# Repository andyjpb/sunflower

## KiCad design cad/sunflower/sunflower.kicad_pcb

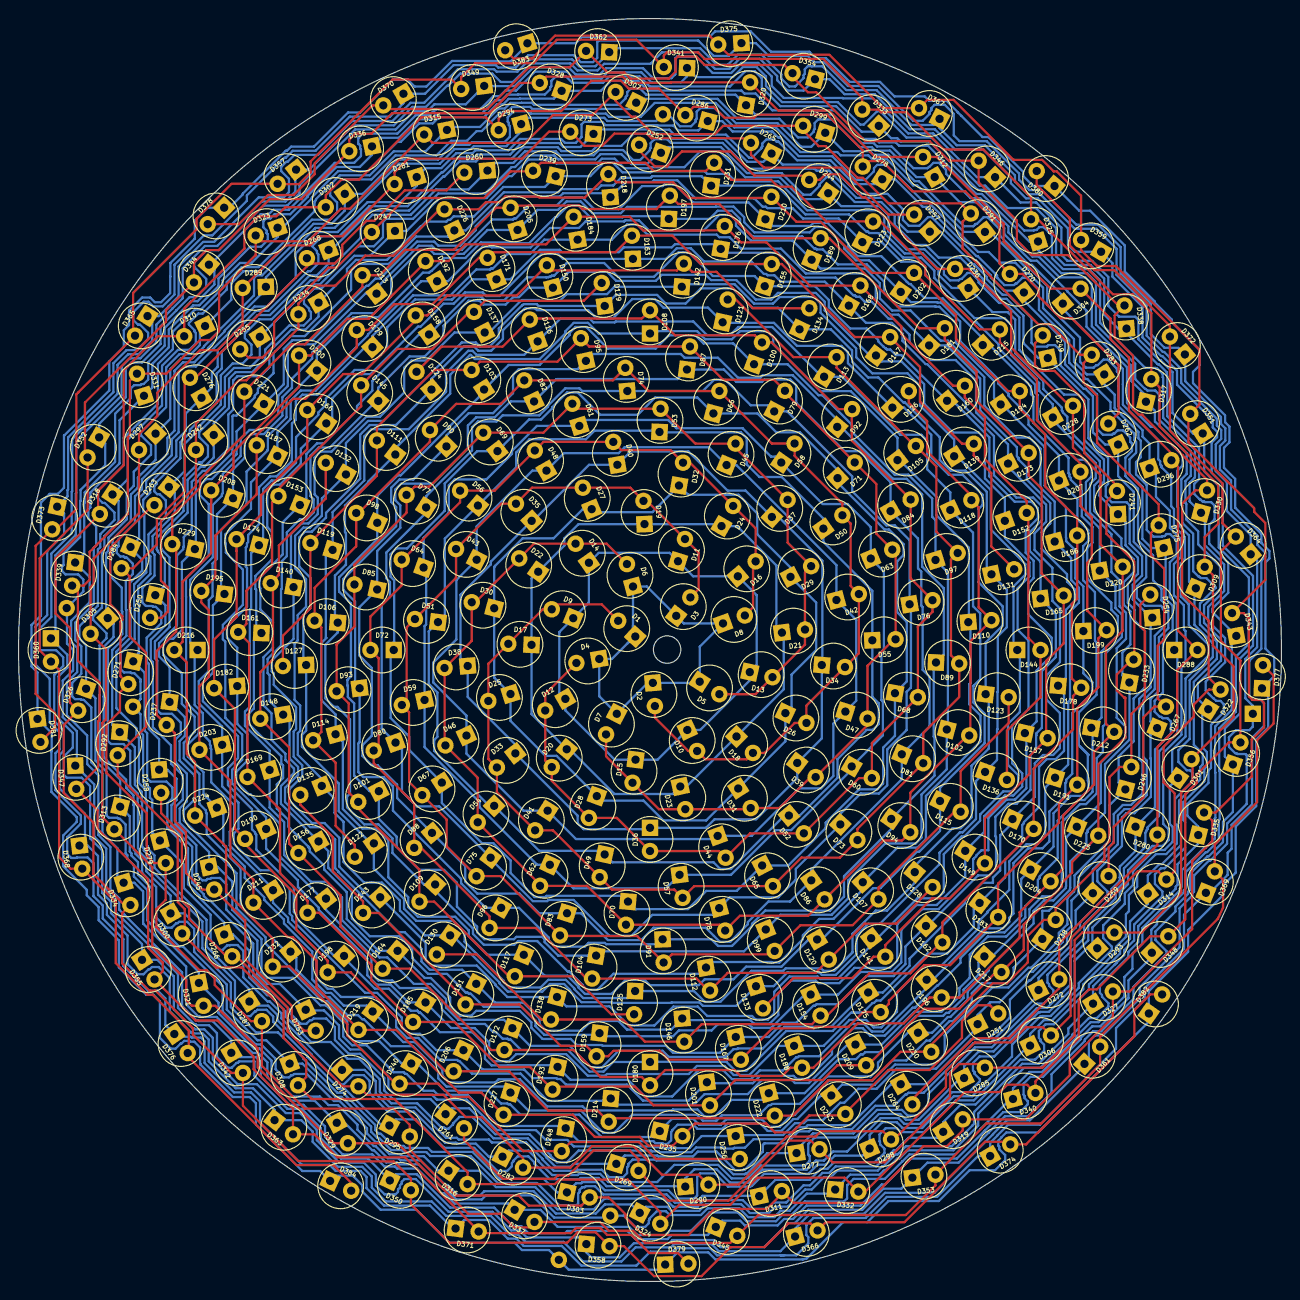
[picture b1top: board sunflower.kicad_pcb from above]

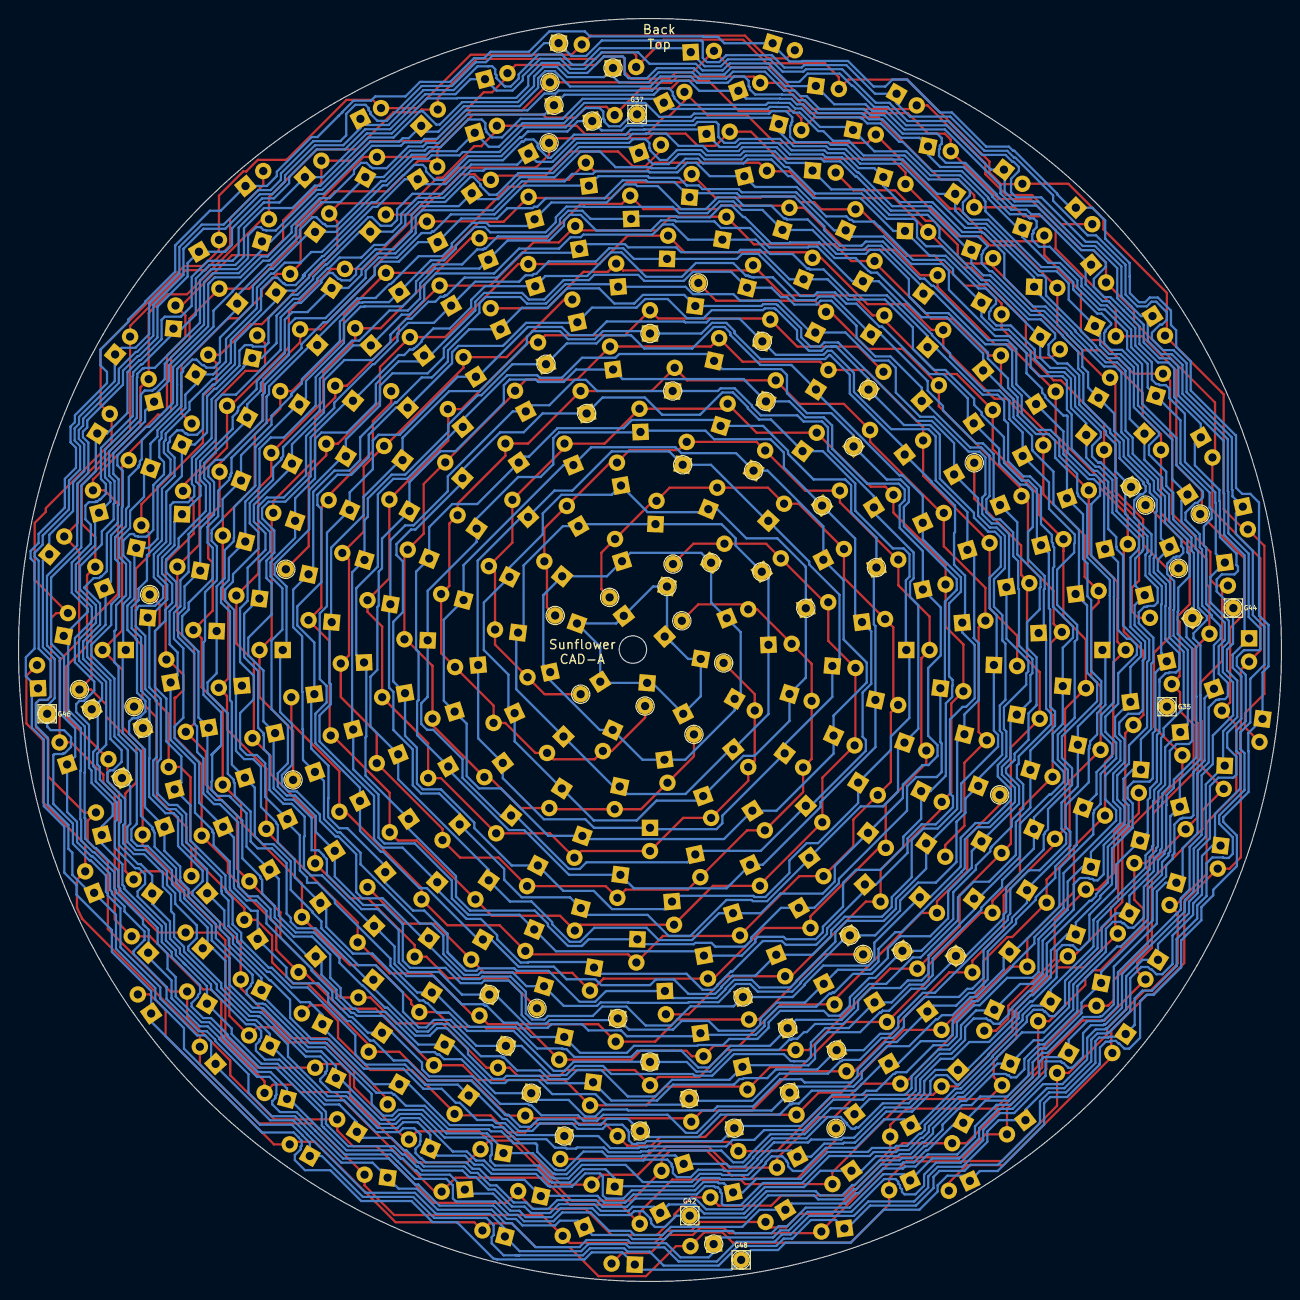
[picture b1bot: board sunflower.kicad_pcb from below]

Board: 2 copper layers, 138.0 x 138.0 mm, 390 parts (6 on the bottom side), 72 nets.

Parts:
D1, D2, D3, D4, D5, D6, D7, D8, D9, D10, D11, D12, D13, D14, D15, D16, D17, D18, D19, D20, D21, D22, D23, D24, D25, D26, D27, D28, D29, D30, D31, D32, D33, D34, D35, D36, D37, D38, D39, D40, D41, D42, D43, D44, D45, D46, D47, D48, D49, D50, D51, D52, D53, D54, D55, D56, D57, D58, D59, D60, D61, D62, D63, D64, D65, D66, D67, D68, D69, D70, D71, D72, D73, D74, D75, D76, D77, D78, D79, D80, D81, D82, D83, D84, D85, D86, D87, D88, D89, D90, D91, D92, D93, D94, D95, D96, D97, D98, D99, D100, D101, D102, D103, D104, D105, D106, D107, D108, D109, D110, D111, D112, D113, D114, D115, D116, D117, D118, D119, D120, D121, D122, D123, D124, D125, D126, D127, D128, D129, D130, D131, D132, D133, D134, D135, D136, D137, D138, D139, D140, D141, D142, D143, D144, D145, D146, D147, D148, D149, D150, D151, D152, D153, D154, D155, D156, D157, D158, D159, D160, D161, D162, D163, D164, D165, D166, D167, D168, D169, D170, D171, D172, D173, D174, D175, D176, D177, D178, D179, D180, D181, D182, D183, D184, D185, D186, D187, D188, D189, D190, D191, D192, D193, D194, D195, D196, D197, D198, D199, D200, D201, D202, D203, D204, D205, D206, D207, D208, D209, D210, D211, D212, D213, D214, D215, D216, D217, D218, D219, D220, D221, D222, D223, D224, D225, D226, D227, D228, D229, D230, D231, D232, D233, D234, D235, D236, D237, D238, D239, D240, D241, D242, D243, D244, D245, D246, D247, D248, D249, D250, D251, D252, D253, D254, D255, D256, D257, D258, D259, D260, D261, D262, D263, D264, D265, D266, D267, D268, D269, D270, D271, D272, D273, D274, D275, D276, D277, D278, D279, D280, D281, D282, D283, D284, D285, D286, D287, D288, D289, D290, D291, D292, D293, D294, D295, D296, D297, D298, D299, D300, D301, D302, D303, D304, D305, D306, D307, D308, D309, D310, D311, D312, D313, D314, D315, D316, D317, D318, D319, D320, D321, D322, D323, D324, D325, D326, D327, D328, D329, D330, D331, D332, D333, D334, D335, D336, D337, D338, D339, D340, D341, D342, D343, D344, D345, D346, D347, D348, D349, D350, D351, D352, D353, D354, D355, D356, D357, D358, D359, D360, D361, D362, D363, D364, D365, D366, D367, D368, D369, D370, D371, D372, D373, D374, D375, D376, D377, D378, D379, D380, D381, D382, D383, D384: LED_Small; LED_D5.0mm
G35, G37, G42, G44, G46, G48: Conn_01x01; Link_Square

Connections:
/matrix-1/GRID1: D1.1, D2.1, D3.1, D4.1, D5.1, D6.1, D7.1, D8.1
/matrix-1/GRID2: D9.1, D10.1, D11.1, D12.1, D13.1, D14.1, D15.1, D16.1
/matrix-1/GRID3: D17.1, D18.1, D19.1, D20.1, D21.1, D22.1, D23.1, D24.1
/matrix-1/GRID4: D25.1, D26.1, D27.1, D28.1, D29.1, D30.1, D31.1, D32.1
/matrix-1/GRID5: D33.1, D34.1, D35.1, D36.1, D37.1, D38.1, D39.1, D40.1
/matrix-1/GRID6: D41.1, D42.1, D43.1, D44.1, D45.1, D46.1, D47.1, D48.1
/matrix-1/GRID7: D49.1, D50.1, D51.1, D52.1, D53.1, D54.1, D55.1, D56.1
/matrix-1/GRID8: D57.1, D58.1, D59.1, D60.1, D61.1, D62.1, D63.1, D64.1
/matrix-1/GRID9: D65.1, D66.1, D67.1, D68.1, D69.1, D70.1, D71.1, D72.1
/matrix-1/GRID10: D73.1, D74.1, D75.1, D76.1, D77.1, D78.1, D79.1, D80.1
/matrix-1/GRID11: D81.1, D82.1, D83.1, D84.1, D85.1, D86.1, D87.1, D88.1
/matrix-1/GRID12: D89.1, D90.1, D91.1, D92.1, D93.1, D94.1, D95.1, D96.1
/matrix-1/GRID13: D97.1, D98.1, D99.1, D100.1, D101.1, D102.1, D103.1, D104.1
/matrix-1/GRID14: D105.1, D106.1, D107.1, D108.1, D109.1, D110.1, D111.1, D112.1
/matrix-1/GRID15: D113.1, D114.1, D115.1, D116.1, D117.1, D118.1, D119.1, D120.1
/matrix-1/GRID16: D121.1, D122.1, D123.1, D124.1, D125.1, D126.1, D127.1, D128.1
/matrix-1/SEG1: D1.2, D9.2, D17.2, D25.2, D33.2, D41.2, D49.2, D57.2, D65.2, D73.2, D81.2, D89.2, D97.2, D105.2, D113.2, D121.2
/matrix-1/SEG2: D2.2, D10.2, D18.2, D26.2, D34.2, D42.2, D50.2, D58.2, D66.2, D74.2, D82.2, D90.2, D98.2, D106.2, D114.2, D122.2
/matrix-1/SEG3: D3.2, D11.2, D19.2, D27.2, D35.2, D43.2, D51.2, D59.2, D67.2, D75.2, D83.2, D91.2, D99.2, D107.2, D115.2, D123.2
/matrix-1/SEG4: D4.2, D12.2, D20.2, D28.2, D36.2, D44.2, D52.2, D60.2, D68.2, D76.2, D84.2, D92.2, D100.2, D108.2, D116.2, D124.2
/matrix-1/SEG5: D5.2, D13.2, D21.2, D29.2, D37.2, D45.2, D53.2, D61.2, D69.2, D77.2, D85.2, D93.2, D101.2, D109.2, D117.2, D125.2
/matrix-1/SEG6: D6.2, D14.2, D22.2, D30.2, D38.2, D46.2, D54.2, D62.2, D70.2, D78.2, D86.2, D94.2, D102.2, D110.2, D118.2, D126.2
/matrix-1/SEG7: D7.2, D15.2, D23.2, D31.2, D39.2, D47.2, D55.2, D63.2, D71.2, D79.2, D87.2, D95.2, D103.2, D111.2, D119.2, D127.2
/matrix-1/SEG8: D8.2, D16.2, D24.2, D32.2, D40.2, D48.2, D56.2, D64.2, D72.2, D80.2, D88.2, D96.2, D104.2, D112.2, D120.2, D128.2
/matrix-2/GRID1: D129.1, D130.1, D131.1, D132.1, D133.1, D134.1, D135.1, D136.1
/matrix-2/GRID2: D137.1, D138.1, D139.1, D140.1, D141.1, D142.1, D143.1, D144.1
/matrix-2/GRID3: D145.1, D146.1, D147.1, D148.1, D149.1, D150.1, D151.1, D152.1
/matrix-2/GRID4: D153.1, D154.1, D155.1, D156.1, D157.1, D158.1, D159.1, D160.1
/matrix-2/GRID5: D161.1, D162.1, D163.1, D164.1, D165.1, D166.1, D167.1, D168.1
/matrix-2/GRID6: D169.1, D170.1, D171.1, D172.1, D173.1, D174.1, D175.1, D176.1
/matrix-2/GRID7: D177.1, D178.1, D179.1, D180.1, D181.1, D182.1, D183.1, D184.1
/matrix-2/GRID8: D185.1, D186.1, D187.1, D188.1, D189.1, D190.1, D191.1, D192.1
/matrix-2/GRID9: D193.1, D194.1, D195.1, D196.1, D197.1, D198.1, D199.1, D200.1
/matrix-2/GRID10: D201.1, D202.1, D203.1, D204.1, D205.1, D206.1, D207.1, D208.1
/matrix-2/GRID11: D209.1, D210.1, D211.1, D212.1, D213.1, D214.1, D215.1, D216.1
/matrix-2/GRID12: D217.1, D218.1, D219.1, D220.1, D221.1, D222.1, D223.1, D224.1
/matrix-2/GRID13: D225.1, D226.1, D227.1, D228.1, D229.1, D230.1, D231.1, D232.1
/matrix-2/GRID14: D233.1, D234.1, D235.1, D236.1, D237.1, D238.1, D239.1, D240.1
/matrix-2/GRID15: D241.1, D242.1, D243.1, D244.1, D245.1, D246.1, D247.1, D248.1
/matrix-2/GRID16: D249.1, D250.1, D251.1, D252.1, D253.1, D254.1, D255.1, D256.1
/matrix-2/SEG1: D129.2, D137.2, D145.2, D153.2, D161.2, D169.2, D177.2, D185.2, D193.2, D201.2, D209.2, D217.2, D225.2, D233.2, D241.2, D249.2
/matrix-2/SEG2: D130.2, D138.2, D146.2, D154.2, D162.2, D170.2, D178.2, D186.2, D194.2, D202.2, D210.2, D218.2, D226.2, D234.2, D242.2, D250.2
/matrix-2/SEG3: D131.2, D139.2, D147.2, D155.2, D163.2, D171.2, D179.2, D187.2, D195.2, D203.2, D211.2, D219.2, D227.2, D235.2, D243.2, D251.2
/matrix-2/SEG4: D132.2, D140.2, D148.2, D156.2, D164.2, D172.2, D180.2, D188.2, D196.2, D204.2, D212.2, D220.2, D228.2, D236.2, D244.2, D252.2
/matrix-2/SEG5: D133.2, D141.2, D149.2, D157.2, D165.2, D173.2, D181.2, D189.2, D197.2, D205.2, D213.2, D221.2, D229.2, D237.2, D245.2, D253.2
/matrix-2/SEG6: D134.2, D142.2, D150.2, D158.2, D166.2, D174.2, D182.2, D190.2, D198.2, D206.2, D214.2, D222.2, D230.2, D238.2, D246.2, D254.2
/matrix-2/SEG7: D135.2, D143.2, D151.2, D159.2, D167.2, D175.2, D183.2, D191.2, D199.2, D207.2, D215.2, D223.2, D231.2, D239.2, D247.2, D255.2
/matrix-2/SEG8: D136.2, D144.2, D152.2, D160.2, D168.2, D176.2, D184.2, D192.2, D200.2, D208.2, D216.2, D224.2, D232.2, D240.2, D248.2, D256.2
/matrix-3/GRID1: D257.1, D258.1, D259.1, D260.1, D261.1, D262.1, D263.1, D264.1
/matrix-3/GRID2: D265.1, D266.1, D267.1, D268.1, D269.1, D270.1, D271.1, D272.1
/matrix-3/GRID3: D273.1, D274.1, D275.1, D276.1, D277.1, D278.1, D279.1, D280.1, G35.1
/matrix-3/GRID4: D281.1, D282.1, D283.1, D284.1, D285.1, D286.1, D287.1, D288.1
/matrix-3/GRID5: D289.1, D290.1, D291.1, D292.1, D293.1, D294.1, D295.1, D296.1, G37.1
/matrix-3/GRID6: D297.1, D298.1, D299.1, D300.1, D301.1, D302.1, D303.1, D304.1
/matrix-3/GRID7: D305.1, D306.1, D307.1, D308.1, D309.1, D310.1, D311.1, D312.1
/matrix-3/GRID8: D313.1, D314.1, D315.1, D316.1, D317.1, D318.1, D319.1, D320.1
/matrix-3/GRID9: D321.1, D322.1, D323.1, D324.1, D325.1, D326.1, D327.1, D328.1
/matrix-3/GRID10: D329.1, D330.1, D331.1, D332.1, D333.1, D334.1, D335.1, D336.1, G42.1
/matrix-3/GRID11: D337.1, D338.1, D339.1, D340.1, D341.1, D342.1, D343.1, D344.1
/matrix-3/GRID12: D345.1, D346.1, D347.1, D348.1, D349.1, D350.1, D351.1, D352.1, G44.1
/matrix-3/GRID13: D353.1, D354.1, D355.1, D356.1, D357.1, D358.1, D359.1, D360.1
/matrix-3/GRID14: D361.1, D362.1, D363.1, D364.1, D365.1, D366.1, D367.1, D368.1, G46.1
/matrix-3/GRID15: D369.1, D370.1, D371.1, D372.1, D373.1, D374.1, D375.1, D376.1
/matrix-3/GRID16: D377.1, D378.1, D379.1, D380.1, D381.1, D382.1, D383.1, D384.1, G48.1
/matrix-3/SEG1: D257.2, D265.2, D273.2, D281.2, D289.2, D297.2, D305.2, D313.2, D321.2, D329.2, D337.2, D345.2, D353.2, D361.2, D369.2, D377.2
/matrix-3/SEG2: D258.2, D266.2, D274.2, D282.2, D290.2, D298.2, D306.2, D314.2, D322.2, D330.2, D338.2, D346.2, D354.2, D362.2, D370.2, D378.2
/matrix-3/SEG3: D259.2, D267.2, D275.2, D283.2, D291.2, D299.2, D307.2, D315.2, D323.2, D331.2, D339.2, D347.2, D355.2, D363.2, D371.2, D379.2
/matrix-3/SEG4: D260.2, D268.2, D276.2, D284.2, D292.2, D300.2, D308.2, D316.2, D324.2, D332.2, D340.2, D348.2, D356.2, D364.2, D372.2, D380.2
/matrix-3/SEG5: D261.2, D269.2, D277.2, D285.2, D293.2, D301.2, D309.2, D317.2, D325.2, D333.2, D341.2, D349.2, D357.2, D365.2, D373.2, D381.2
/matrix-3/SEG6: D262.2, D270.2, D278.2, D286.2, D294.2, D302.2, D310.2, D318.2, D326.2, D334.2, D342.2, D350.2, D358.2, D366.2, D374.2, D382.2
/matrix-3/SEG7: D263.2, D271.2, D279.2, D287.2, D295.2, D303.2, D311.2, D319.2, D327.2, D335.2, D343.2, D351.2, D359.2, D367.2, D375.2, D383.2
/matrix-3/SEG8: D264.2, D272.2, D280.2, D288.2, D296.2, D304.2, D312.2, D320.2, D328.2, D336.2, D344.2, D352.2, D360.2, D368.2, D376.2, D384.2

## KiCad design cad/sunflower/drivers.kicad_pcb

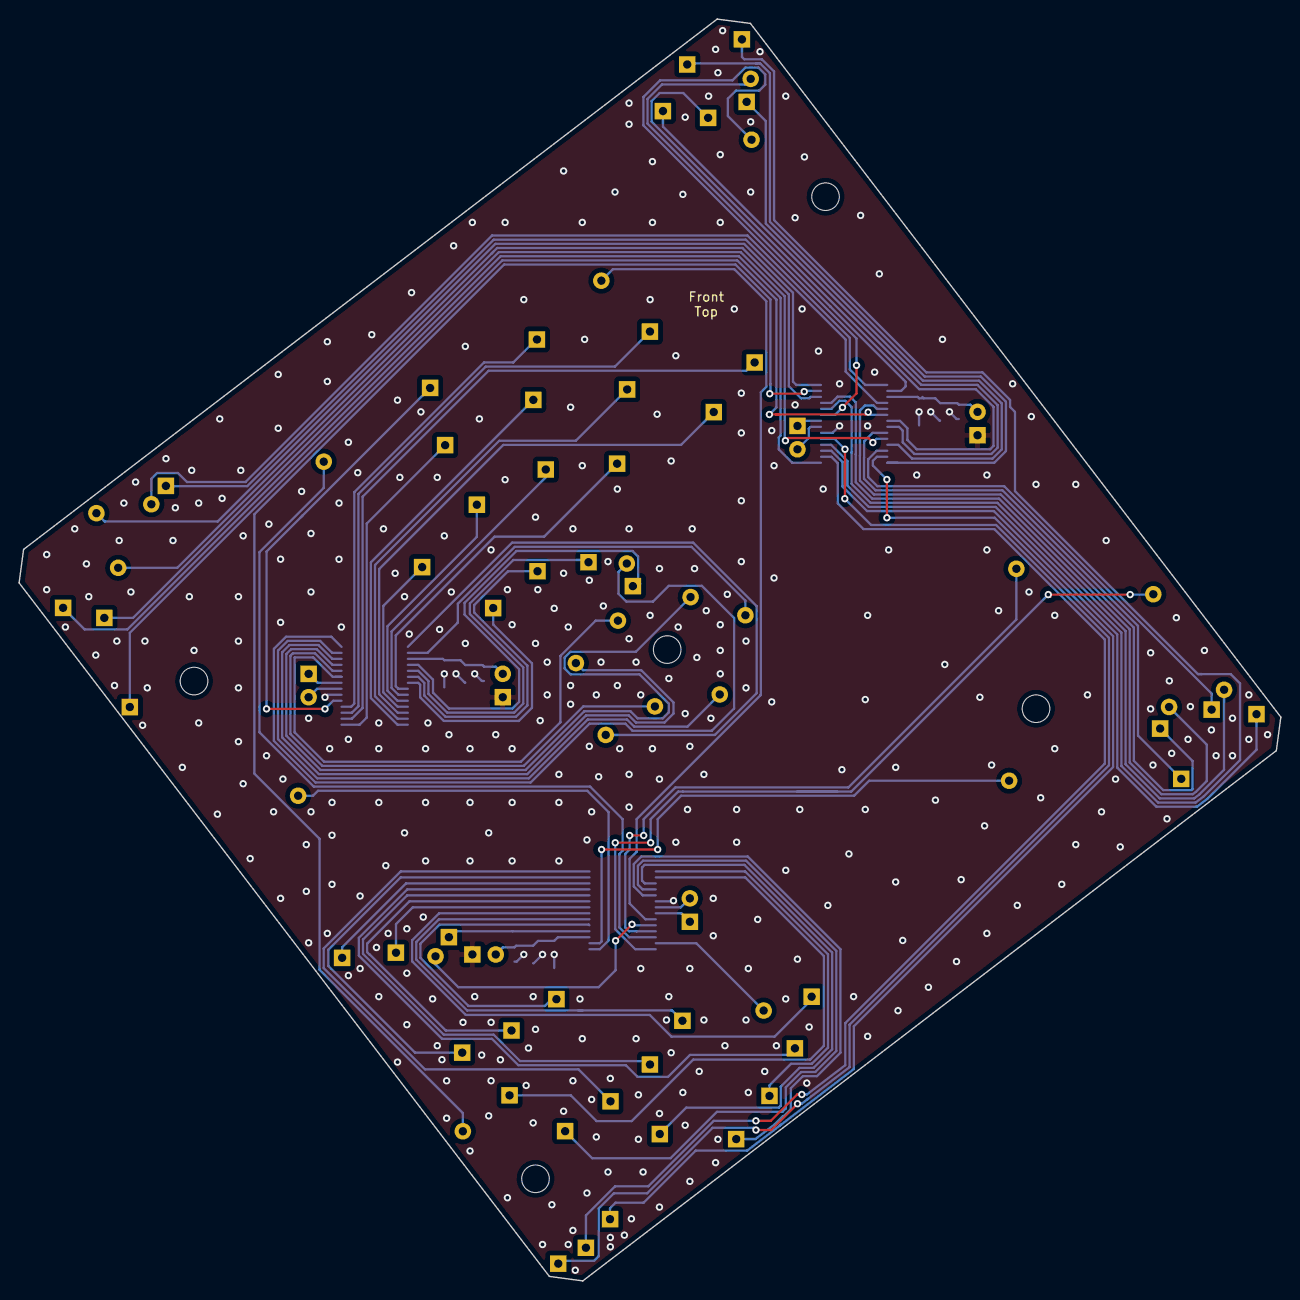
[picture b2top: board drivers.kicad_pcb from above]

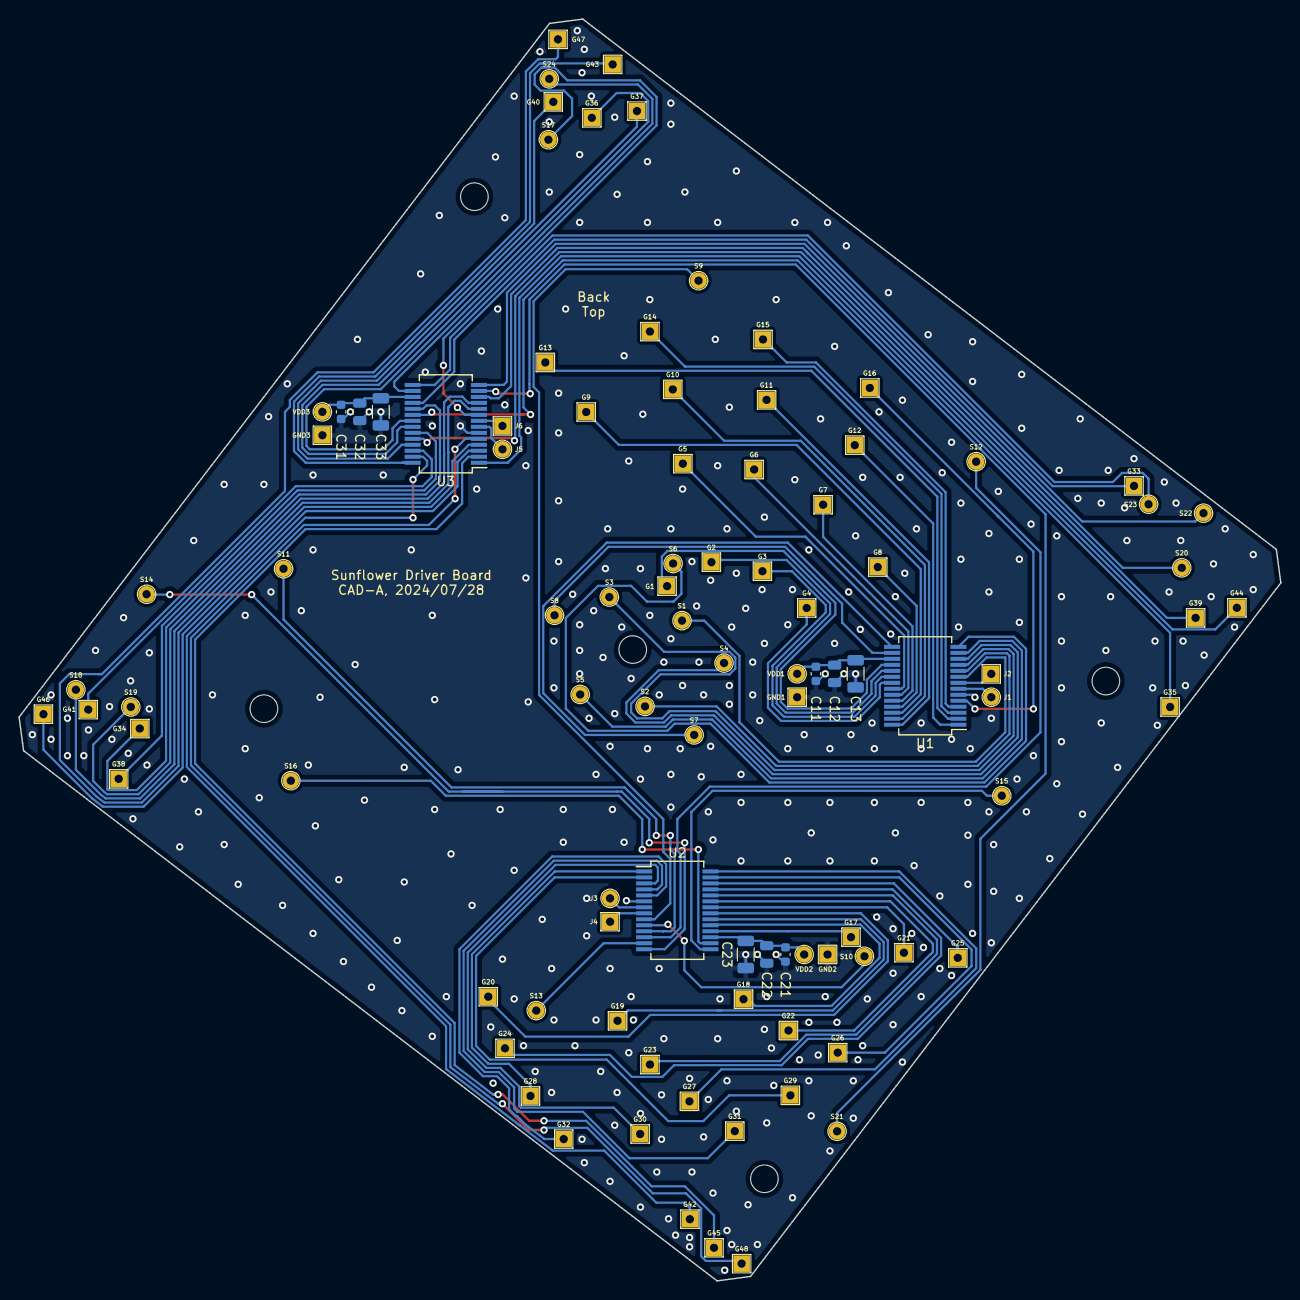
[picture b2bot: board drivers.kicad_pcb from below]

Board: 2 copper layers, 137.0 x 137.0 mm, 96 parts (96 on the bottom side), 80 nets.

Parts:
C11, C21, C31: 100n; C_0603_1608Metric
C12, C22, C32: 10u; C_0805_2012Metric
C13, C23, C33: 47u; C_1206_3216Metric
G1, G2, G3, G4, G5, G6, G7, G8, G9, G10, G11, G12, G13, G14, G15, G16, G17, G18, G19, G20, G21, G22, G23, G24, G25, G26, G27, G28, G29, G30, G31, G32, G33, G34, G35, G36, G37, G38, G39, G40, G41, G42, G43, G44, G45, G46, G47, G48: Conn_01x01; Link_Square
GND1, GND2, GND3: Conn_01x01; Link_Square
J1, J3, J5: Conn_01x01; Link_Round
J2, J4, J6: Conn_01x01; Link_Square
S1, S2, S3, S4, S5, S6, S7, S8, S9, S10, S11, S12, S13, S14, S15, S16, S17, S18, S19, S20, S21, S22, S23, S24: Conn_01x01; Link_Round
U1, U2, U3: TM1640; SSOP-28_5.3x10.2mm_P0.65mm
VDD1, VDD2, VDD3: Conn_01x01; Link_Round

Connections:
5V: C11.1, C12.1, C13.1, C21.1, C22.1, C23.1, C31.1, C32.1, C33.1, U1.17, U2.17, U3.17, VDD1.1, VDD2.1, VDD3.1
/matrix-1/DIN: J1.1, U1.7
/matrix-1/GRID1: G1.1, U1.18
/matrix-1/GRID2: G2.1, U1.19
/matrix-1/GRID3: G3.1, U1.20
/matrix-1/GRID4: G4.1, U1.21
/matrix-1/GRID5: G5.1, U1.22
/matrix-1/GRID6: G6.1, U1.23
/matrix-1/GRID7: G7.1, U1.24
/matrix-1/GRID8: G8.1, U1.25
/matrix-1/GRID9: G9.1, U1.26
/matrix-1/GRID10: G10.1, U1.27
/matrix-1/GRID11: G11.1, U1.28
/matrix-1/GRID12: G12.1, U1.1
/matrix-1/GRID13: G13.1, U1.2
/matrix-1/GRID14: G14.1, U1.3
/matrix-1/GRID15: G15.1, U1.4
/matrix-1/GRID16: G16.1, U1.5
/matrix-1/SCLK: J2.1, U1.8
/matrix-1/SEG1: S1.1, U1.9
/matrix-1/SEG2: S2.1, U1.10
/matrix-1/SEG3: S3.1, U1.11
/matrix-1/SEG4: S4.1, U1.12
/matrix-1/SEG5: S5.1, U1.13
/matrix-1/SEG6: S6.1, U1.14
/matrix-1/SEG7: S7.1, U1.15
/matrix-1/SEG8: S8.1, U1.16
/matrix-2/DIN: J3.1, U2.7
/matrix-2/GRID1: G17.1, U2.18
/matrix-2/GRID2: G18.1, U2.19
/matrix-2/GRID3: G19.1, U2.20
/matrix-2/GRID4: G20.1, U2.21
/matrix-2/GRID5: G21.1, U2.22
/matrix-2/GRID6: G22.1, U2.23
/matrix-2/GRID7: G23.1, U2.24
/matrix-2/GRID8: G24.1, U2.25
/matrix-2/GRID9: G25.1, U2.26
/matrix-2/GRID10: G26.1, U2.27
/matrix-2/GRID11: G27.1, U2.28
/matrix-2/GRID12: G28.1, U2.1
/matrix-2/GRID13: G29.1, U2.2
/matrix-2/GRID14: G30.1, U2.3
/matrix-2/GRID15: G31.1, U2.4
/matrix-2/GRID16: G32.1, U2.5
/matrix-2/SCLK: J4.1, U2.8
/matrix-2/SEG1: S9.1, U2.9
/matrix-2/SEG2: S10.1, U2.10
/matrix-2/SEG3: S11.1, U2.11
/matrix-2/SEG4: S12.1, U2.12
/matrix-2/SEG5: S13.1, U2.13
/matrix-2/SEG6: S14.1, U2.14
/matrix-2/SEG7: S15.1, U2.15
/matrix-2/SEG8: S16.1, U2.16
/matrix-3/DIN: J5.1, U3.7
/matrix-3/GRID1: G33.1, U3.18
/matrix-3/GRID2: G34.1, U3.19
/matrix-3/GRID3: G35.1, U3.20
/matrix-3/GRID4: G36.1, U3.21
/matrix-3/GRID5: G37.1, U3.22
/matrix-3/GRID6: G38.1, U3.23
/matrix-3/GRID7: G39.1, U3.24
/matrix-3/GRID8: G40.1, U3.25
/matrix-3/GRID9: G41.1, U3.26
/matrix-3/GRID10: G42.1, U3.27
/matrix-3/GRID11: G43.1, U3.28
/matrix-3/GRID12: G44.1, U3.1
/matrix-3/GRID13: G45.1, U3.2
/matrix-3/GRID14: G46.1, U3.3
/matrix-3/GRID15: G47.1, U3.4
/matrix-3/GRID16: G48.1, U3.5
/matrix-3/SCLK: J6.1, U3.8
/matrix-3/SEG1: S17.1, U3.9
/matrix-3/SEG2: S18.1, U3.10
/matrix-3/SEG3: S19.1, U3.11
/matrix-3/SEG4: S20.1, U3.12
/matrix-3/SEG5: S21.1, U3.13
/matrix-3/SEG6: S22.1, U3.14
/matrix-3/SEG7: S23.1, U3.15
/matrix-3/SEG8: S24.1, U3.16
GND: C11.2, C12.2, C13.2, C21.2, C22.2, C23.2, C31.2, C32.2, C33.2, GND1.1, GND2.1, GND3.1, U1.6, U2.6, U3.6

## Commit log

2024-07-30 Initial notes and resources.
    + Datasheet for TM1640 LED Driver
    + seedsDYNAMIC.xls from https://web.archive.org/web/20090530011347/http://www.mcs.surrey.ac.uk/Personal/R.Knott/Fibonacci/seedsDYNAMIC.xls
    + Project notes
2024-07-30 Tool to position sunflower seeds in SVG and on a Kicad PCB.
2024-07-30 Spreadsheet for deciding interboard connections
    Where should the square(-ish) driver board connect to the
    round sunflower board?
    We need a connection for each GRID and SEG line for each
    LED driver.
2024-07-30 Script to annotate sunflower PCB with GRID and SEG silkscreens
    A script to mark the back of the sunflower PCB with the
    LED legs that need to be left uncut because they connect
    GRID and SEG lines to the driver board.
    This also marks the extra pads that have been added to
    the sunflower board where there is no existing LED leg
    that will work. In these cases, the pads can end up being
2024-07-30 Kicad project files
    + Schematic
    + Sunflower PCB
    + Driver PCB
    + Custom LED and Link footprints
2024-07-30 Files generated from scripts as part of the design process.
2024-07-30 Backup PCB files
2024-07-30 CAD-A Gerbers to JLCPCB specs
    As per
    https://jlcpcb.com/help/article/42-How-to-generate-Gerber-and-Drill-files-in-KiCad-4
    and
    https://jlcpcb.com/help/article/2201-how-to-generate-gerber-and-drill-files-in-kicad-8
    I tried to use the KiCad 8 settings but needed the KiCad 4 guide to find
    the right menu options (File -> Plot) and to compare UI differences with
2024-07-30 Gerber zip files as provided to JLCPCB for manufacturing.
2024-08-27 PCB Soldering & Assembly Instructions
    Typed up from the notes I made as I did it.
